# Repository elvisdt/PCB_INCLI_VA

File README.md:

# INCLI-VA — Inclinómetro de chasis CAN/BLE

Proyecto KiCad 10 jerárquico. Hoja raíz: `INCLI-VA.kicad_sch` (00_top).

## Estructura
| Ruta | Contenido |
|---|---|
| `sheets/10_power_input` | Conectores Phoenix MSTB 2,5 de 5.08 mm GF (J1, J2), fusible F101 SF-2410FPA200W-2, LM74930-Q1 (diodo ideal, corte por OV, breaker de 1 A), TVS, filtro LC → +VPROT. C105 (hold-up): `DNP = PROTO`, se monta en PROD. Desde rc6: UVLO desde VBAT_F (R113 + R106) y D104 = BAV23C (D1 de VA a VS, TI fig. 8-1) |
| `sheets/20_buck_5v` | Buck no aislado U201 LMR38010SQDDARQ1 (PROTO: LMR38010SDDAR): +VPROT → +5V_VEH, 5.02 V / 1 A a 400 kHz. Sin pines jerárquicos |
| `sheets/30_regulation` | Desde el riel de 5 V: buck TPS62A02-Q1 → +3V3_D, LDO LP5907-Q1 → +3V3_A, divisores VMON |
| `sheets/40_mcu_esp32s3` | MCU ESP32-S3-WROOM-1-N8R2 (único MCU), USB-C nativo con ESD, UART0, BOOT/RESET |
| `sheets/40_mcu_kw45` | Solo referencia: no está en la jerarquía |
| `sheets/50_sensors` | SCL3300-D01 (inclinómetro), ASM330LHH (IMU), AS5147U (ángulo de pluma, solo variante ROT) en SPI compartido |
| `sheets/60_can` | ADM3055E (CAN aislado con isoPower, único aislamiento de la placa) desde el TWAI del ESP32-S3 (CAN clásico, J1939). Terminación partida 2 × 60.4 Ω + 4.7 nF, activada con JP601 (puente de soldadura en la cara inferior, abierto por defecto; unido = 120 Ω, nodo en el extremo del bus). ESD externo ESD2CAN24-Q1 como DNP |
| `sheets/70_output_ch` | 1 canal low-side (drenador abierto, relé externo), instanciado 2 veces (DO1, DO2): buffer 74AHCT1G126 (3.3 → 5 V), DMN10H220LQ 100 V, zener de gate y SMAJ58A. Sin latch de sobrecorriente (retirado); diagnóstico como huella DNP en PROTO |
| `sheets/80_supervision` | U801 TPS3828-33-Q1 (supervisor de +3V3_D + watchdog, WDI ← IO17), LED verde/rojo (DNP en PROD), VAR_ID0/1/2 por 0 Ω a GND |
| `lib/` | Librería propia: símbolos (`INCLI-VA.kicad_sym`), huellas (`.pretty`), 3D |
| `docs/` | Propuestas ESP32-S3 (vigente) y KW45 (descartada), datasheets |
| `fab/` | Gerbers, BOM por variante, pick & place |

## Convenciones
- Rieles/masas: símbolos de potencia de la lib `INCLI-VA`: `+VPROT +5V_VEH +3V3_D +3V3_A GND_VEH GND_CAN`. Nunca `GND` genérico.
  - Opción B (no aislada): toda la placa usa GND_VEH. GND_CAN (lado bus del ADM3055E) es el único dominio aislado.
  - `GND_ISO` y `+5V_ISO` siguen en la librería, pero ya no se usan.
- Señales entre hojas: pines jerárquicos; en el top se unen por etiquetas del mismo nombre.
- Prefijos de red por dominio: `VEH_`, `ISO_`, `BUS_`.
- Campos por componente: `MPN`, `Manufacturer`, `LCSC`, `Datasheet`, `Alt_MPN`, `Variant` (CAN, OUT, ROT, CABIN), `Notes` y `DNP`. `LCSC` es el código LCSC/JLC del `MPN` (vacío si LCSC no lo lista).
- `MPN_PROTO`, `Manufacturer_PROTO` y `LCSC_PROTO`: solo cuando el prototipo usa un equivalente distinto del MPN de producción (por ejemplo, la versión comercial de una pieza -Q1, un pasivo JLC Basic o un sustituto aceptado; ver `docs/BOM_SOURCING.md`). `Manufacturer_PROTO` solo si cambia el fabricante. El BOM de prototipo usa el campo `_PROTO` si existe y, si no, el de producción.
- **Prototipo = producción:** es el mismo esquemático; solo cambia qué se monta. El campo `DNP` define los dos BOM:
  - vacío: se monta siempre.
  - `PROTO`: no se monta en el prototipo.
  - `PROD`: no se monta en producción.
  - `PROTO,PROD`: huella reservada.
  - El atributo `dnp` de KiCad refleja el BOM de prototipo.

## Entorno
- Vehículos de 12 V y 24 V nominales. Transitorios: ISO 7637-2 e ISO 16750-2, con load dump **suprimido** (24 V: ≤ 58 V). La entrada también bloquea un load dump sin suprimir (202 V); las salidas DO no.

## MCU
El diseño usa solo el **ESP32-S3-WROOM-1** (`sheets/40_mcu_esp32s3`). La KW45 queda descartada; su hoja se conserva como referencia, fuera de la jerarquía.
CAN: TWAI nativo (CAN clásico, J1939) directo al ADM3055E; no hay controlador CAN FD.

## Requisitos para el firmware
- Salidas DO1/DO2 (`70_output_ch`): no hay latch de sobrecorriente (retirado el 2026-10-28); un corto de la carga a +V no queda limitado por hardware. El diagnóstico (DIAG) es DNP en PROTO y se monta en PROD.
- Arranque del motor en vehículos de 12 V y load dump de 24 V (corte por OV del LM74930, ≤ 350 ms): sin C105 (DNP en PROTO) la placa se reinicia (vale desde rc6; en rc5 la placa no arrancaba por el UVLO, hallazgo R-01). El firmware debe arrancar limpio tras un brownout (sin estado corrupto, salidas abiertas hasta reinicializar).
- Watchdog externo (U801): patear WDI (IO17) cada ≤ 0.5 s (timeout mínimo 0.9 s). Una vez inicializado, no dejar IO17 en alta impedancia (eso deshabilita el watchdog), salvo antes de dormir más de 0.9 s.
- VAR_ID (IO4 = ID0, IO5 = ID1, IO8 = ID2): activar los pull-ups internos y leer al arrancar. ID1 ID0: 11 base | 10 CAN | 01 solo DO | 00 CAN + DO. ID2 reservado para CABIN. ROT se detecta por SPI (AS5147U responde).
- AS5147U (modo 3.3 V): poner a 1 el bit **NOISESET** (DS000639 v1-04, fig. 8) y usar CRC/paridad en todas las tramas.
- SCL3300: protocolo fuera de trama (la respuesta llega en la trama siguiente), **TLH ≥ 10 µs** con CSB alto entre tramas (Doc. 4921, tiempos SPI), CRC en cada respuesta y secuencia de arranque (SW reset, modo, espera, STATUS limpio). Modos 1 o 2 para el rango completo.
- No reemplazar U401 por variantes de flash de 1.8 V ni de PSRAM octal (IO35–IO37 e IO47/IO48).
- Radio: stack BLE **NimBLE**; WiFi desactivado en operación normal (solo para OTA en taller). El hardware se dimensiona igual con WiFi activo.

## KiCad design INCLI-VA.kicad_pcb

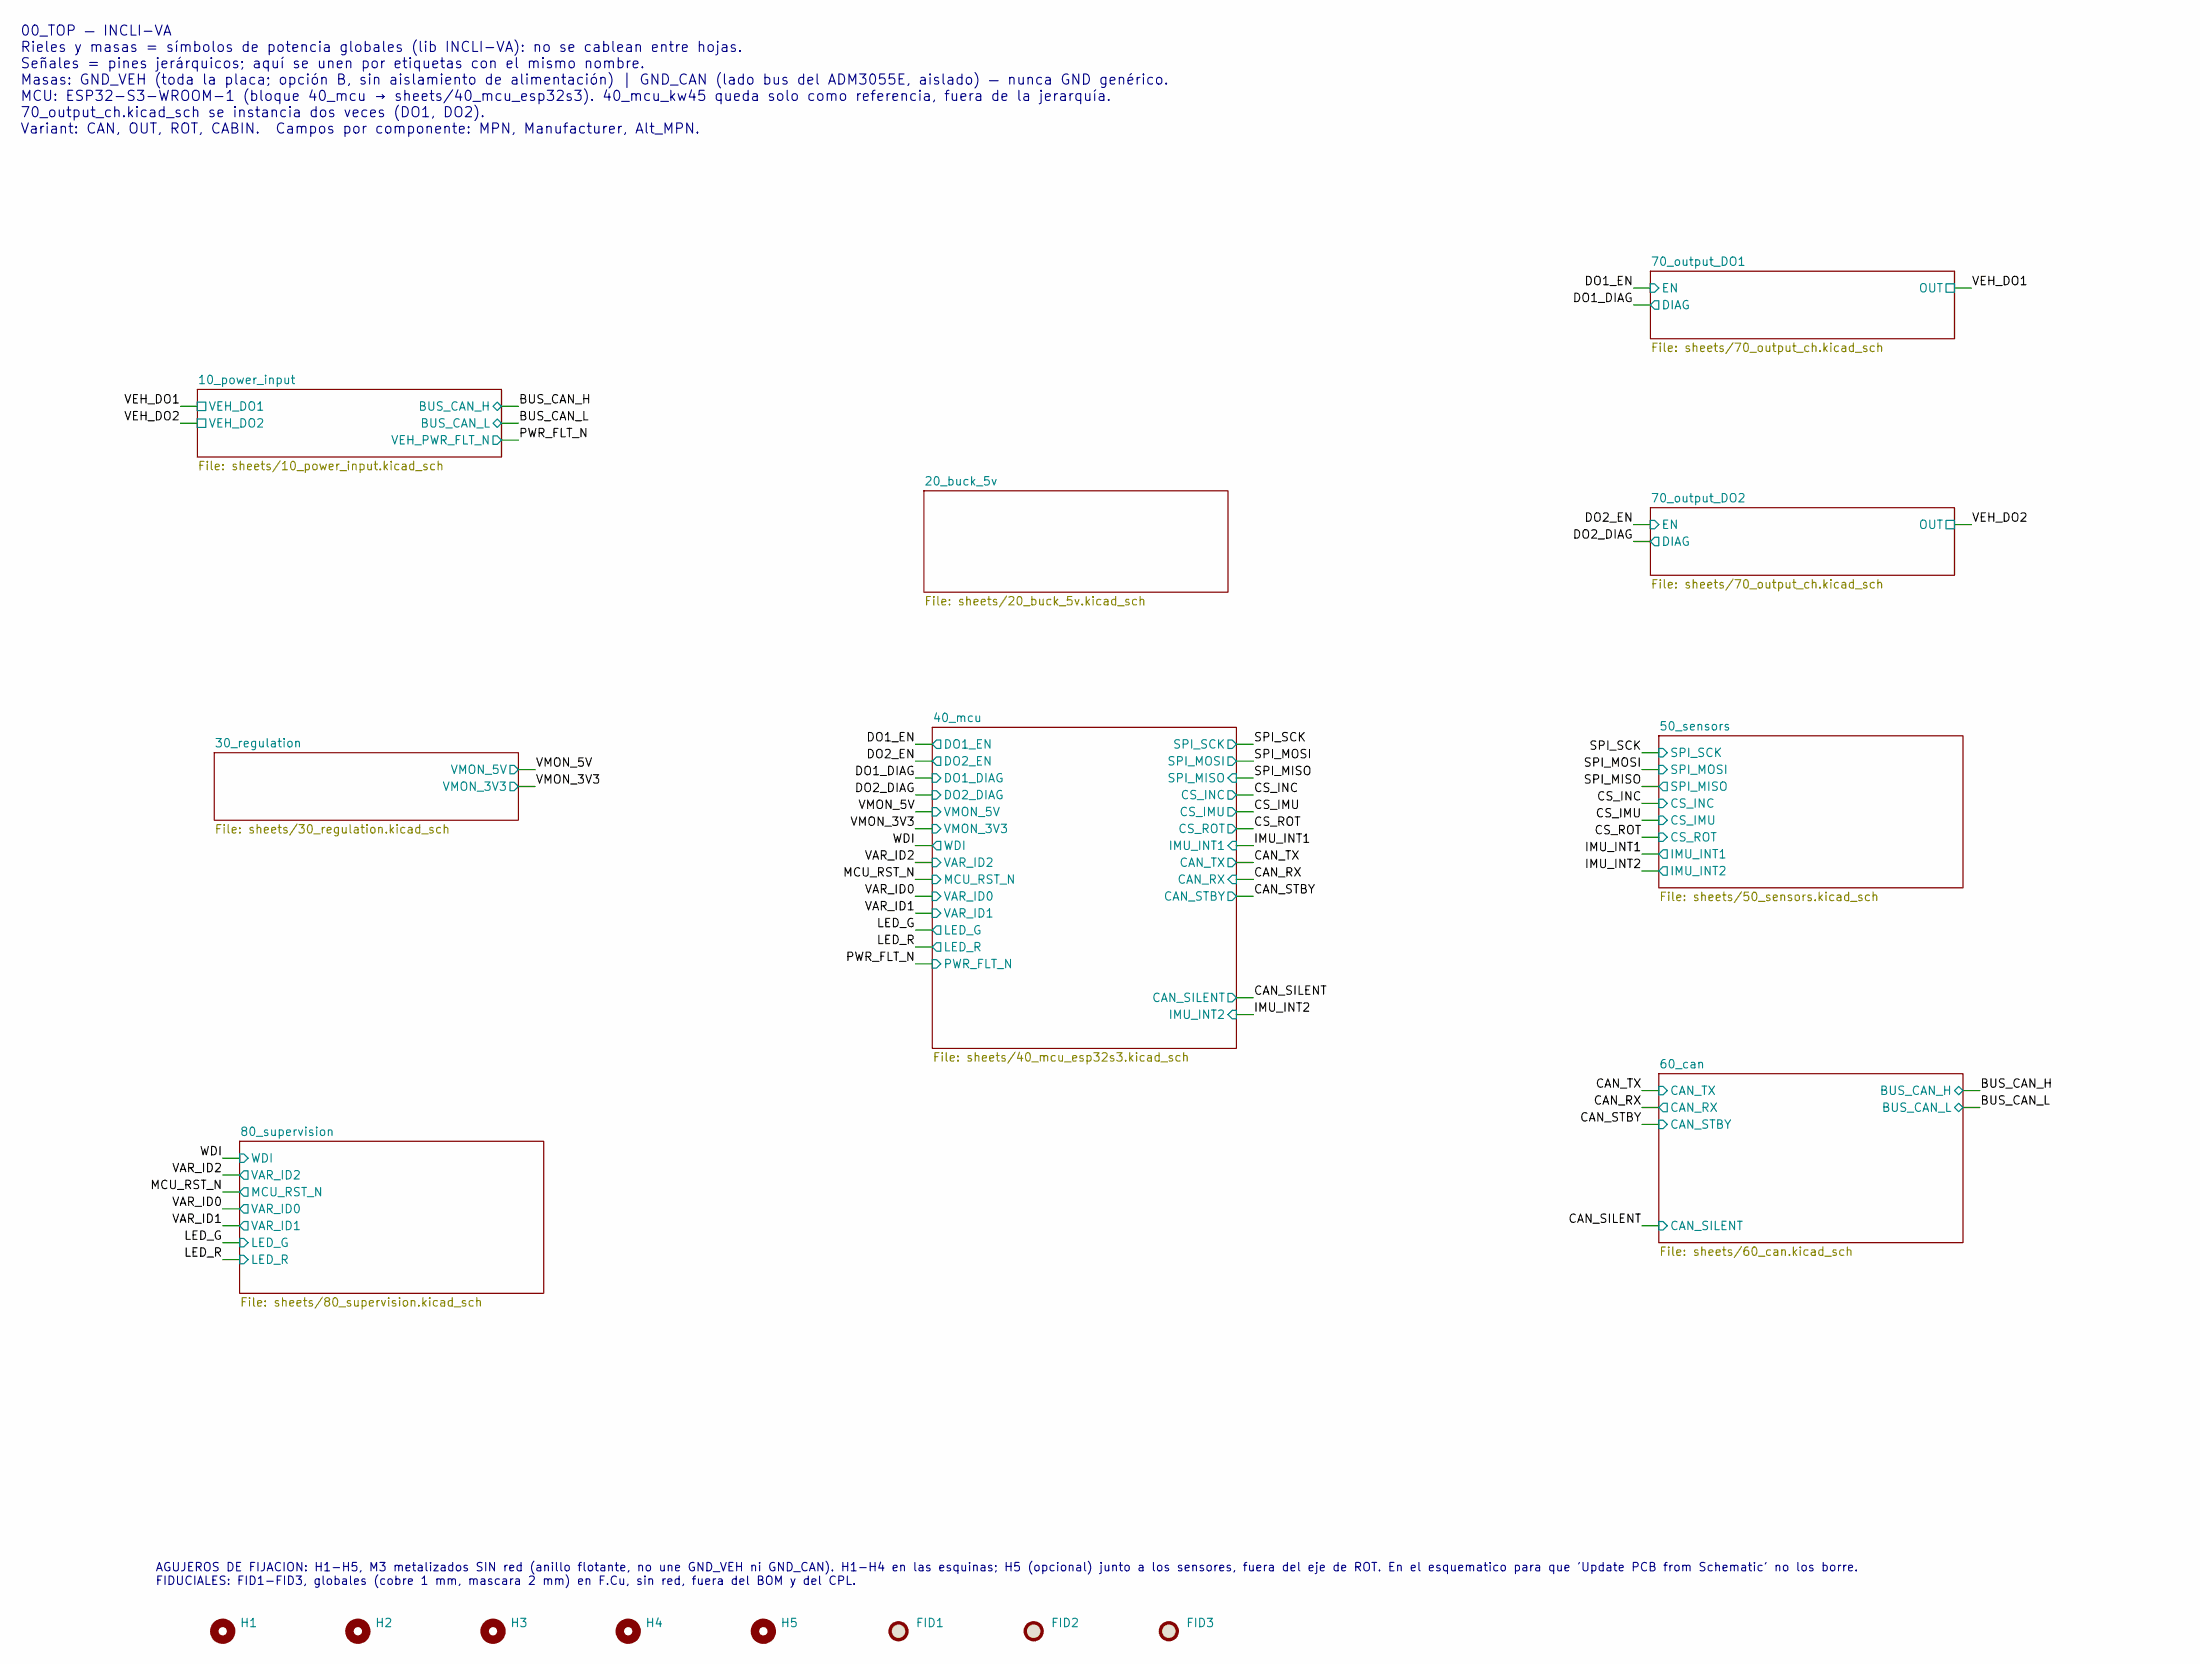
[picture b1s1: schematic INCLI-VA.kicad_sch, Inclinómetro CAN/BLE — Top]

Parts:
FID1, FID2, FID3: Fiducial; Fiducial_1mm_Mask2mm; MPN N/A (fiducial de cobre, sin componente)
H1, H2, H3, H4, H5: MountingHole_M3; MountingHole_3.2mm_M3_Pad; MPN N/A (agujero PTH sin red)

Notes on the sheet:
AGUJEROS DE FIJACION: H1-H5, M3 metalizados SIN red (anillo flotante, no une GND_VEH ni GND_CAN). H1-H4 en las esquinas; H5 (opcional) junto a los sensores, fuera del eje de ROT. En el esquematico para que 'Update PCB from Schematic' no los borre. FIDUCIALES: FID1-FID3, globales (cobre 1 mm, mascar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
00_TOP — INCLI-VA Rieles y masas = símbolos de potencia globales (lib INCLI-VA): no se cablean entre hojas. Señales = pines jerárquicos; aquí se unen por etiquetas con el mismo nombre. Masas: GND_VEH (toda la placa; opción B, sin aislamiento de alimentación) | GND_CAN (lado bus del ADM3055E, aislad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

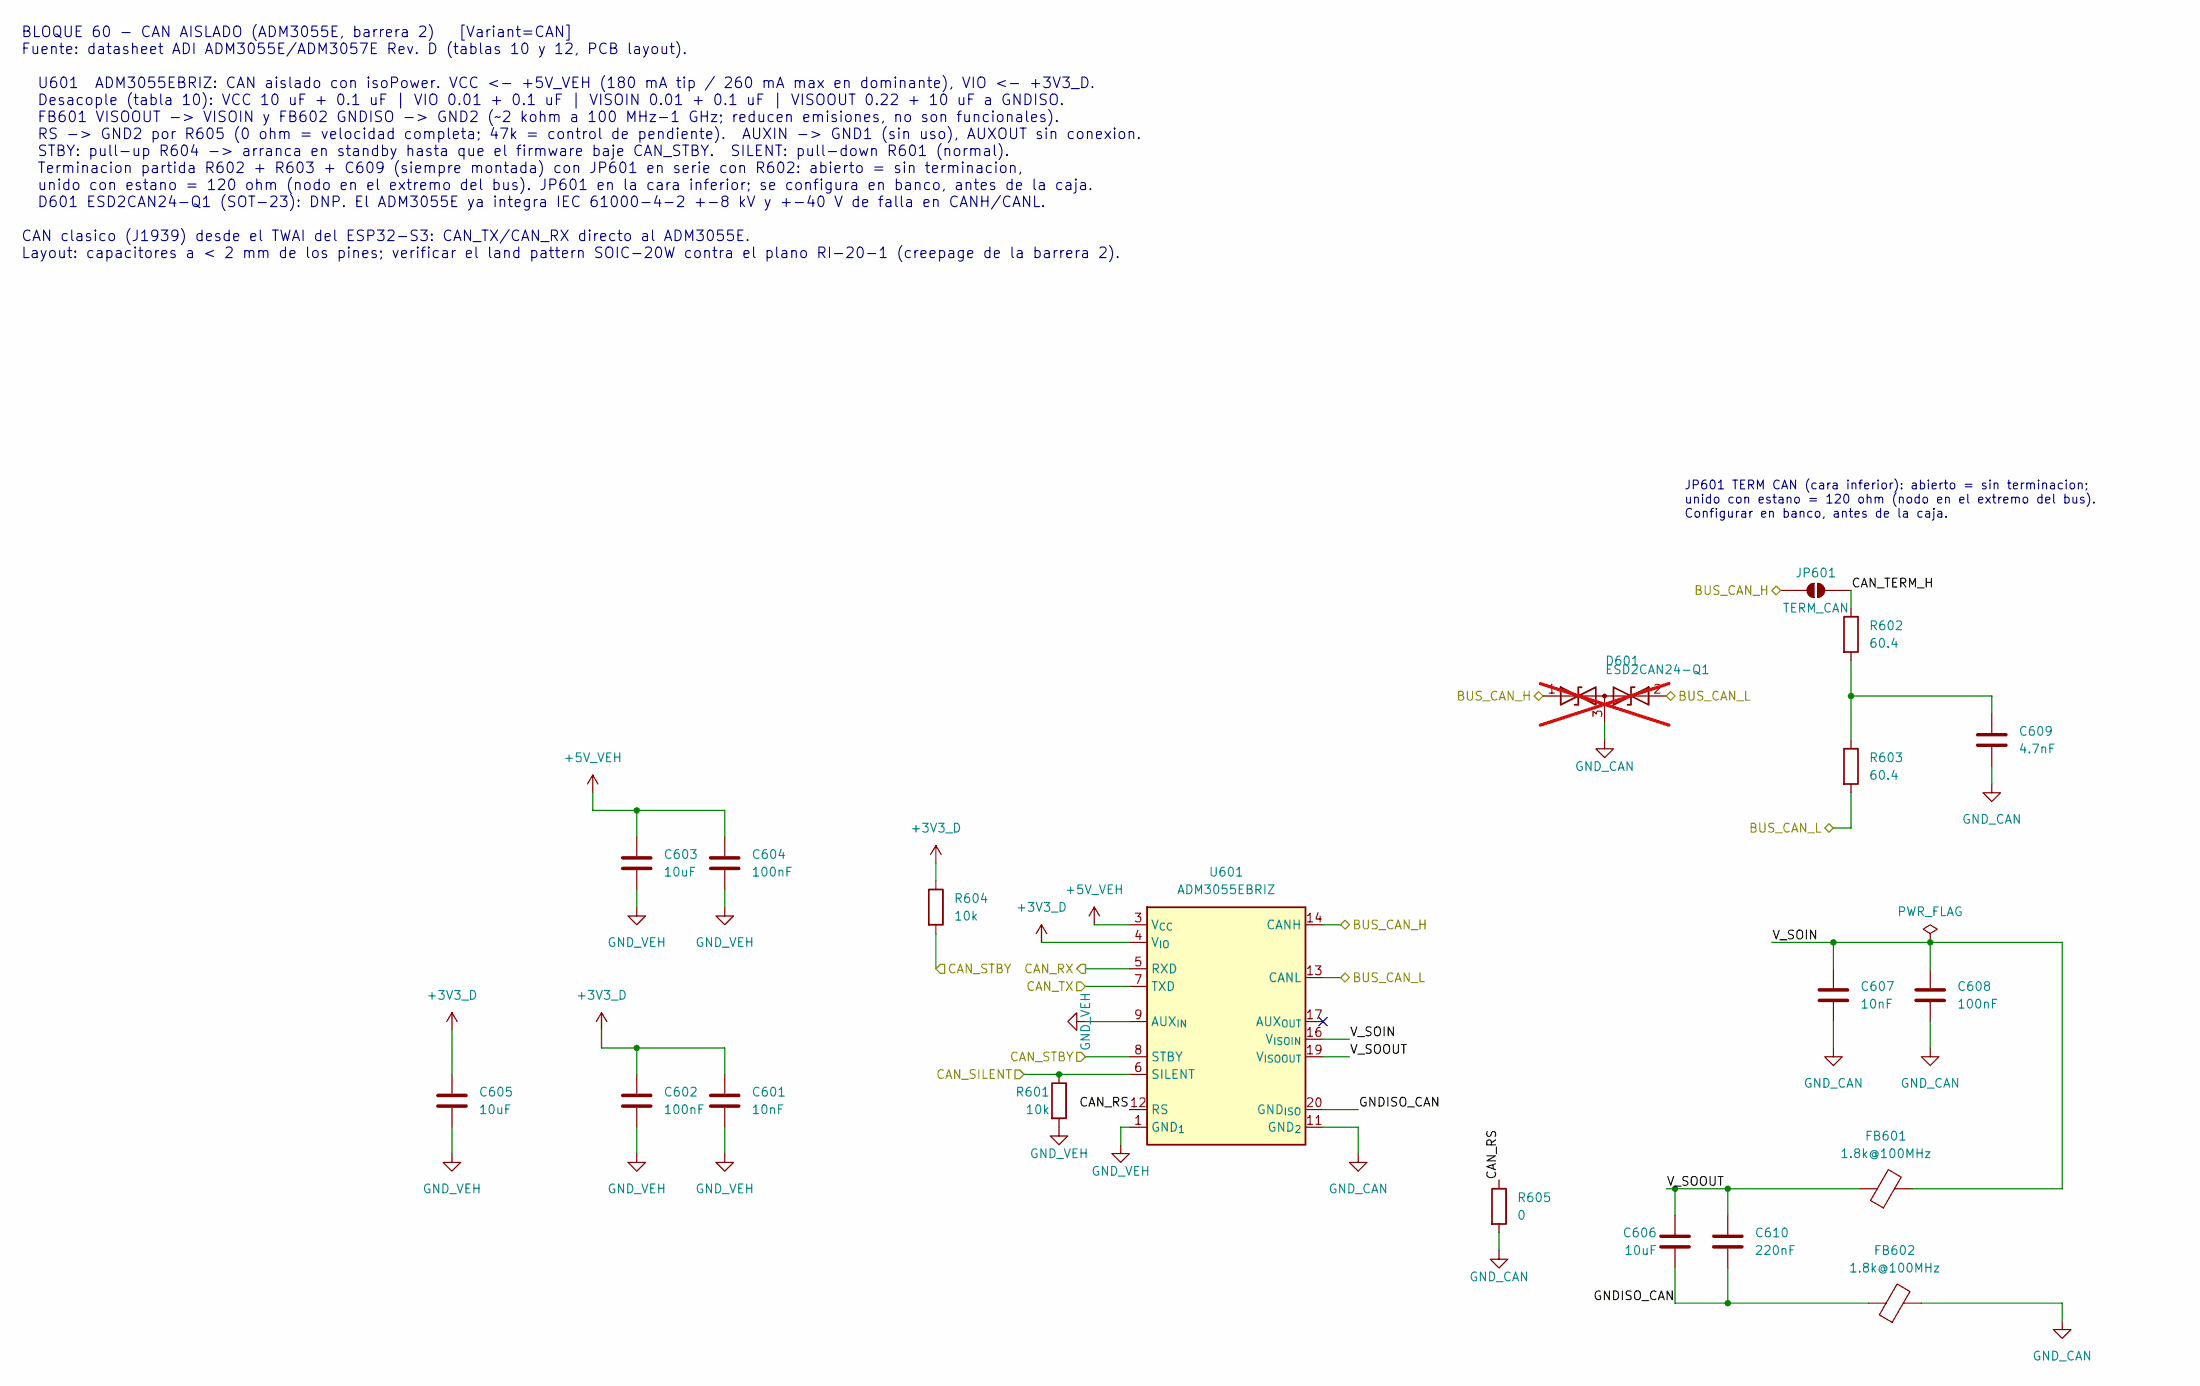
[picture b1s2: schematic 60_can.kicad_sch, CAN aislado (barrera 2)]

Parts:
C601, C607: 10nF; C_0603_1608Metric; MPN GCM188R71H103KA37D; LCSC C85863
C602, C604, C608: 100nF; C_0603_1608Metric; MPN GCM188R72A104KA64D; LCSC C415406
C603, C605, C606: 10uF; C_0805_2012Metric; MPN GCM21BR71A106KE22L; LCSC C126586
C609: 4.7nF; C_0603_1608Metric; MPN GCM188R72A472KA37D; LCSC C426631
C610: 220nF; C_0603_1608Metric; MPN GCM188R71E224KA55D; LCSC C161217
D601: ESD2CAN24-Q1; SOT-23; MPN ESD2CAN24DBZRQ1; LCSC C5736151; not fitted
FB601, FB602: 1.8k@100MHz; L_0603_1608Metric; MPN BLM18BD182SN1D; LCSC C113020
JP601: TERM_CAN; SolderJumper-2_P1.3mm_Open_RoundedPad1.0x1.5mm; MPN N/A (puente de soldadura en el PCB)
R601, R604: 10k; R_0603_1608Metric; MPN AC0603FR-0710KL; LCSC C116677
R602, R603: 60.4; R_0603_1608Metric; MPN AC0603FR-0760R4L; LCSC C144645
R605: 0; R_0603_1608Metric; MPN AC0603JR-070RL; LCSC C141796
U601: ADM3055E; SOIC-20W_7.5x12.8mm_P1.27mm; MPN ADM3055EBRIZ; LCSC C658104

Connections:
+3V3_D: C601.1, C602.1, C605.1, R604.1, U601.4 (V_{IO}); also elsewhere on the board
+5V_VEH: C603.1, C604.1, U601.3 (V_{CC}); also elsewhere on the board
/60_can/CAN_RS: R605.1, U601.12 (RS)
/60_can/CAN_TERM_H: JP601.2 (B), R602.1
/60_can/GNDISO_CAN: C606.2, C610.2, FB602.1, U601.18 (GND_{ISO}), U601.20 (GND_{ISO})
/60_can/V_SOIN: C607.1, C608.1, FB601.2, U601.16 (V_{ISOIN})
/60_can/V_SOOUT: C606.1, C610.1, FB601.1, U601.19 (V_{ISOOUT})
/BUS_CAN_H: D601.1 (A1), JP601.1 (A), U601.14 (CANH); also elsewhere on the board
/BUS_CAN_L: D601.2 (A2), R603.2, U601.13 (CANL); also elsewhere on the board
/CAN_RX: U601.5 (RXD); also elsewhere on the board
/CAN_SILENT: R601.1, U601.6 (SILENT); also elsewhere on the board
/CAN_STBY: R604.2, U601.8 (STBY); also elsewhere on the board
/CAN_TX: U601.7 (TXD); also elsewhere on the board
GND_CAN: C607.2, C608.2, C609.2, D601.3 (common), FB602.2, R605.2, U601.11 (GND_{2}), U601.15 (GND_{2}); also elsewhere on the board
GND_VEH: C601.2, C602.2, C603.2, C604.2, C605.2, R601.2, U601.1 (GND_{1}), U601.2 (GND_{1}), U601.9 (AUX_{IN}), U601.10 (GND_{1}); also elsewhere on the board
unnamed: C609.1, R602.2, R603.1

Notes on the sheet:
BLOQUE 60 - CAN AISLADO (ADM3055E, barrera 2) [Variant=CAN] Fuente: datasheet ADI ADM3055E/ADM3057E Rev. D (tablas 10 y 12, PCB layout). U601 ADM3055EBRIZ: CAN aislado con isoPower. VCC <- +5V_VEH (180 mA tip / 260 mA max en dominante), VIO <- +3V3_D. Desacople (tabla 10): VCC 10 uF + 0.1 uF | VIO 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
JP601 TERM CAN (cara inferior): abierto = sin terminacion; unido con estano = 120 ohm (nodo en el extremo del bus). Configurar en banco, antes de la caja.

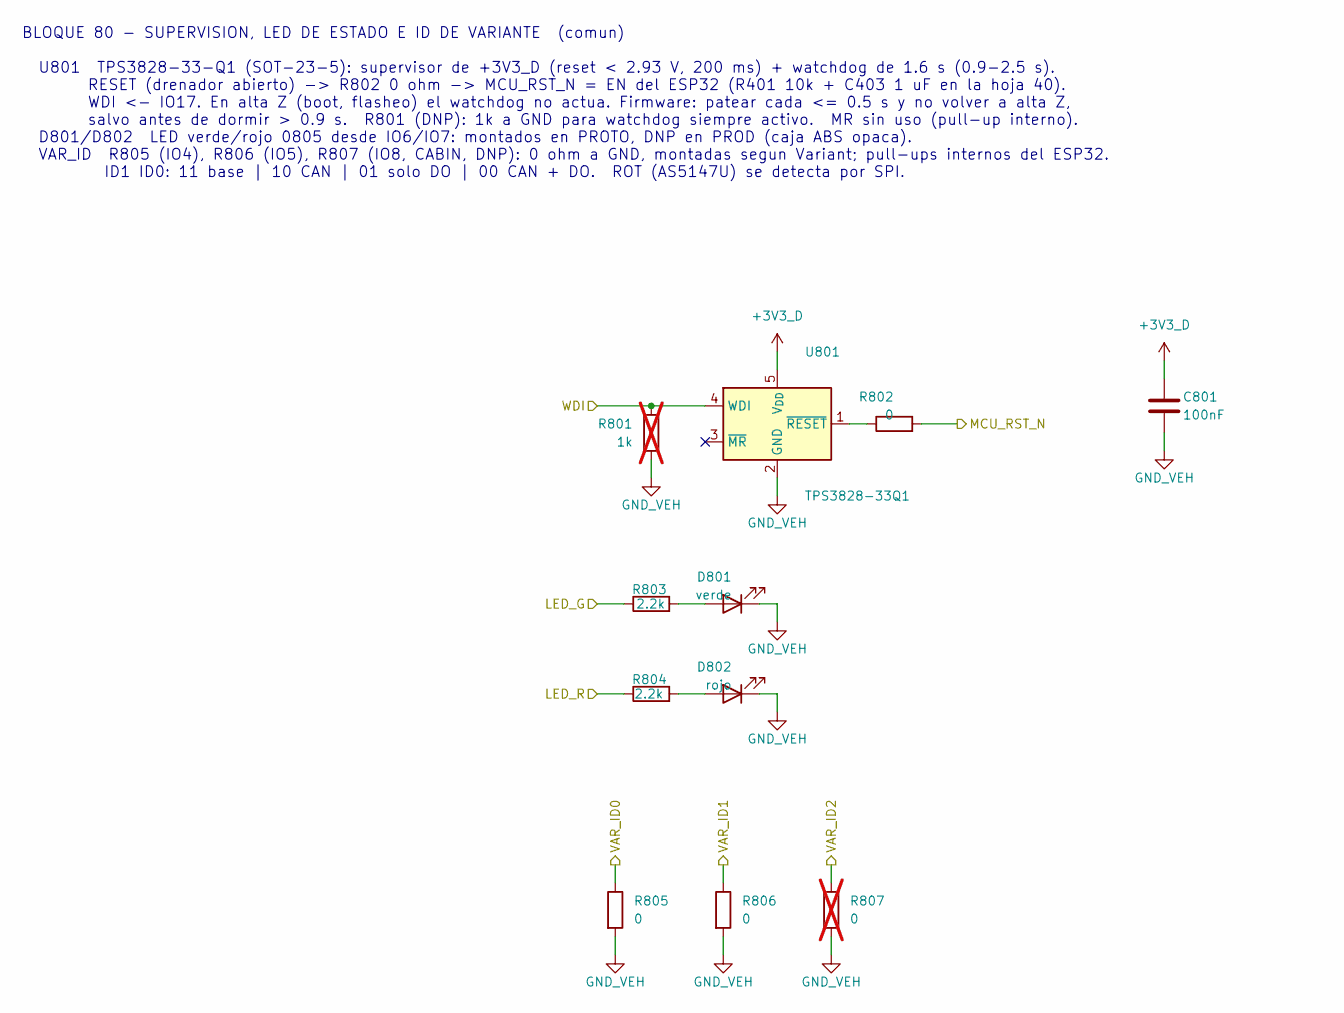
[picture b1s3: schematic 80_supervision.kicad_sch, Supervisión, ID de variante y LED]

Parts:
C801: 100nF; C_0603_1608Metric; MPN GCM188R72A104KA64D; LCSC C415406
D801: verde; LED_0805_2012Metric; MPN LTST-C171KGKT; LCSC C98224
D802: rojo; LED_0805_2012Metric; MPN LTST-C171KRKT; LCSC C284871
R801: 1k; R_0603_1608Metric; MPN AC0603FR-071KL; LCSC C116692; not fitted
R802, R805, R806: 0; R_0603_1608Metric; MPN AC0603JR-070RL; LCSC C141796
R803, R804: 2.2k; R_0603_1608Metric; MPN AC0603FR-072K2L; LCSC C125931
R807: 0; R_0603_1608Metric; MPN AC0603JR-070RL; LCSC C141796; not fitted
U801: TPS3828-33Q1; SOT-23-5; MPN TPS3828-33QDBVRQ1; LCSC C2872895

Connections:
+3V3_D: C801.1, U801.5 (V_{DD}); also elsewhere on the board
/LED_G: R803.1; also elsewhere on the board
/LED_R: R804.1; also elsewhere on the board
/MCU_RST_N: R802.2; also elsewhere on the board
/VAR_ID0: R805.1; also elsewhere on the board
/VAR_ID1: R806.1; also elsewhere on the board
/VAR_ID2: R807.1; also elsewhere on the board
/WDI: R801.1, U801.4 (WDI); also elsewhere on the board
GND_VEH: C801.2, D801.1 (K), D802.1 (K), R801.2, R805.2, R806.2, R807.2, U801.2 (GND); also elsewhere on the board
unnamed: D801.2 (A), R803.2
unnamed: D802.2 (A), R804.2
unnamed: R802.1, U801.1 (~RESET)

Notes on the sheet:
BLOQUE 80 - SUPERVISION, LED DE ESTADO E ID DE VARIANTE (comun) U801 TPS3828-33-Q1 (SOT-23-5): supervisor de +3V3_D (reset < 2.93 V, 200 ms) + watchdog de 1.6 s (0.9-2.5 s). RESET (drenador abierto) -> R802 0 ohm -> MCU_RST_N = EN del ESP32 (R401 10k + C403 1 uF en la hoja 40). WDI <- IO17. En alta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

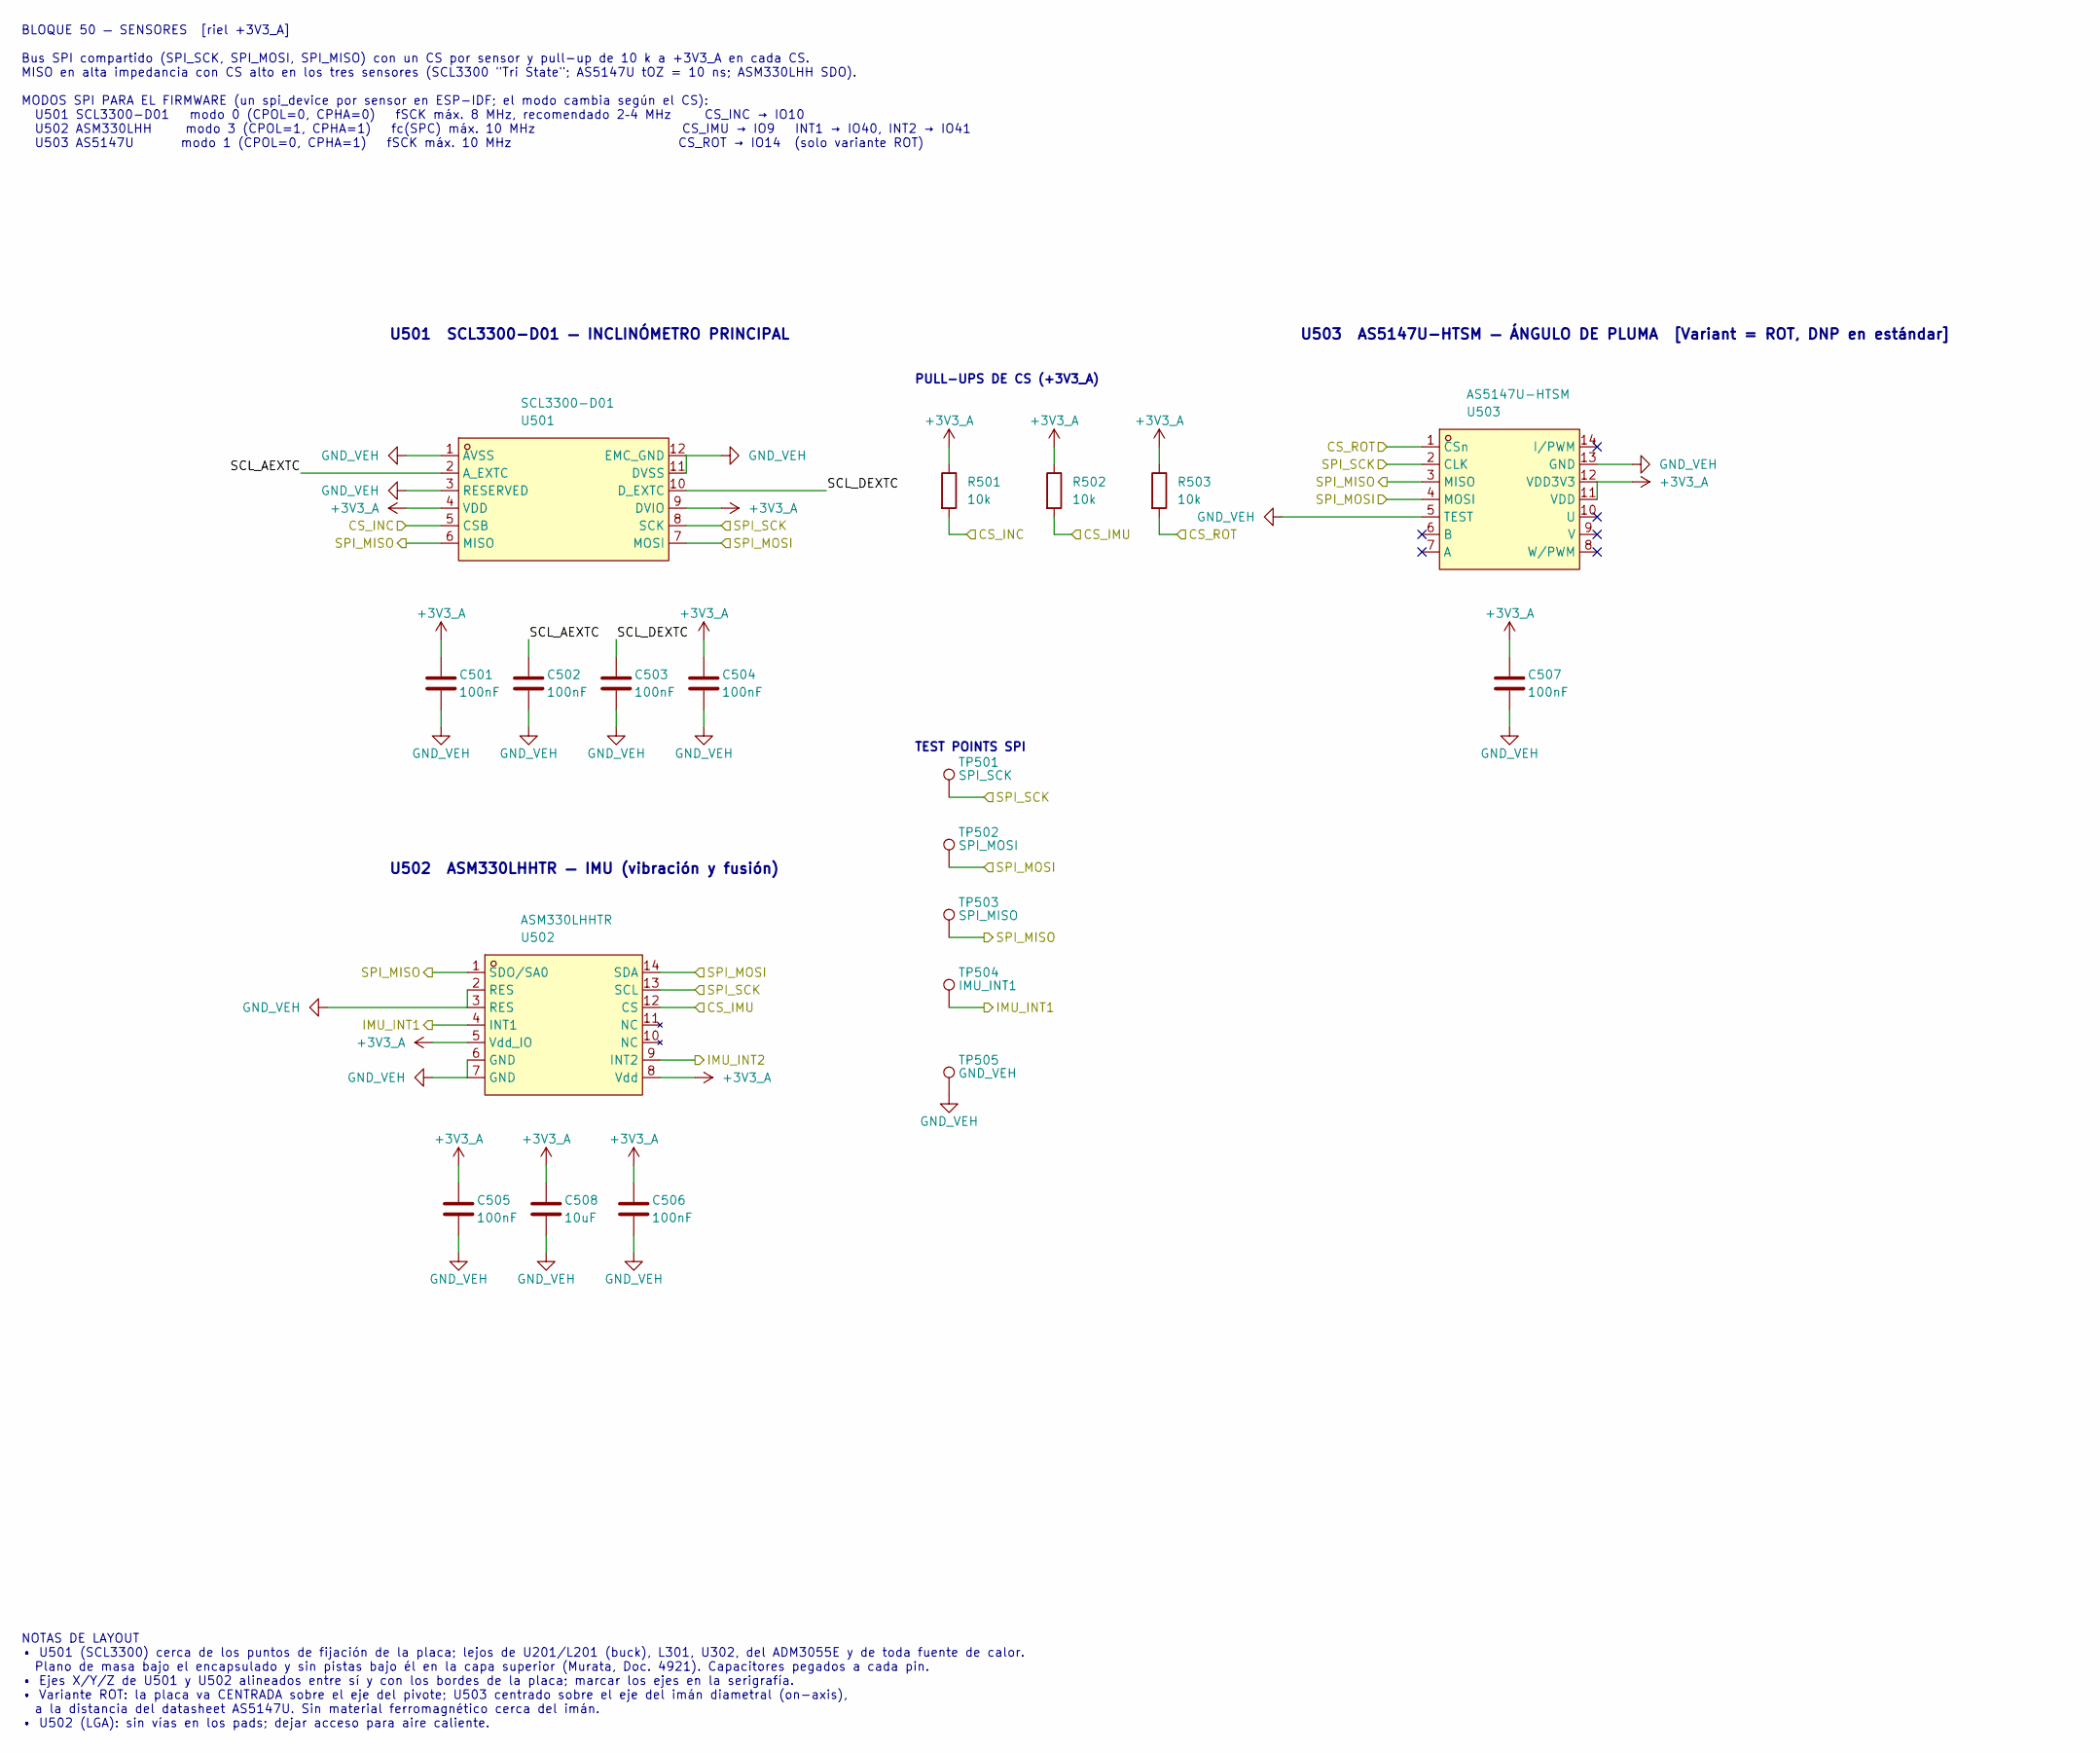
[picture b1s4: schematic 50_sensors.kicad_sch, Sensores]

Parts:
C501, C502, C503, C504, C505, C506, C507: 100nF; C_0603_1608Metric; MPN GCM188R72A104KA64D; LCSC C415406
C508: 10uF; C_0805_2012Metric; MPN GCM21BR71A106KE22L; LCSC C126586
R501, R502, R503: 10k; R_0603_1608Metric; MPN AC0603FR-0710KL; LCSC C116677
TP501: SPI_SCK; TestPoint_Pad_D1.5mm
TP502: SPI_MOSI; TestPoint_Pad_D1.5mm
TP503: SPI_MISO; TestPoint_Pad_D1.5mm
TP504: IMU_INT1; TestPoint_Pad_D1.5mm
TP505: GND_VEH; TestPoint_THTPad_D2.5mm_Drill1.2mm
U501: SCL3300-D01; DFL-12_L8.6-W7.0-P1.00-LS7.6-BL; MPN SCL3300-D01; LCSC C22416657
U502: ASM330LHHTR; LGA-14_3x2.5mm_P0.5mm_LayoutBorder3x4y; MPN ASM330LHHTR; LCSC C459826
U503: AS5147U-HTSM; TSSOP-14_4.4x5mm_P0.65mm; MPN AS5147U-HTSM; LCSC C38675951

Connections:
+3V3_A: C501.1, C504.1, C505.1, C506.1, C507.1, C508.1, R501.1, R502.1, R503.1, U501.4 (VDD), U501.9 (DVIO), U502.5 (Vdd_IO), U502.8 (Vdd), U503.11 (VDD), U503.12 (VDD3V3); also elsewhere on the board
/50_sensors/SCL_AEXTC: C502.1, U501.2 (A_EXTC)
/50_sensors/SCL_DEXTC: C503.1, U501.10 (D_EXTC)
/CS_IMU: R502.2, U502.12 (CS); also elsewhere on the board
/CS_INC: R501.2, U501.5 (CSB); also elsewhere on the board
/CS_ROT: R503.2, U503.1 (CSn); also elsewhere on the board
/IMU_INT1: TP504.1 (1_1), U502.4 (INT1); also elsewhere on the board
/IMU_INT2: U502.9 (INT2); also elsewhere on the board
/SPI_MISO: TP503.1 (1_1), U501.6 (MISO), U502.1 (SDO/SA0), U503.3 (MISO); also elsewhere on the board
/SPI_MOSI: TP502.1 (1_1), U501.7 (MOSI), U502.14 (SDA), U503.4 (MOSI); also elsewhere on the board
/SPI_SCK: TP501.1 (1_1), U501.8 (SCK), U502.13 (SCL), U503.2 (CLK); also elsewhere on the board
GND_VEH: C501.2, C502.2, C503.2, C504.2, C505.2, C506.2, C507.2, C508.2, TP505.1, U501.1 (AVSS), U501.3 (RESERVED), U501.11 (DVSS), U501.12 (EMC_GND), U502.2 (RES), U502.3 (RES), U502.6 (GND), U502.7 (GND), U503.5 (TEST), U503.13 (GND); also elsewhere on the board

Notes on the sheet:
NOTAS DE LAYOUT • U501 (SCL3300) cerca de los puntos de fijación de la placa; lejos de U201/L201 (buck), L301, U302, del ADM3055E y de toda fuente de calor. Plano de masa bajo el encapsulado y sin pistas bajo él en la capa superior (Murata, Doc. 4921). Capacitores pegados a cada pin. • Ejes X/Y/Z d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
TEST POINTS SPI
U502 ASM330LHHTR — IMU (vibración y fusión)
U501 SCL3300-D01 — INCLINÓMETRO PRINCIPAL
U503 AS5147U-HTSM — ÁNGULO DE PLUMA [Variant = ROT, DNP en estándar]
BLOQUE 50 — SENSORES [riel +3V3_A] Bus SPI compartido (SPI_SCK, SPI_MOSI, SPI_MISO) con un CS por sensor y pull-up de 10 k a +3V3_A en cada CS. MISO en alta impedancia con CS alto en los tres sensores (SCL3300 "Tri State"; AS5147U tOZ = 10 ns; ASM330LHH SDO). MODOS SPI PARA EL FIRMWARE (un spi_devi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
PULL-UPS DE CS (+3V3_A)

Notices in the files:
parts and their libraries:
License: Apache-2.0
